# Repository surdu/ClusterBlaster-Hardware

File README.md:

# ClusterBlaster Hardware

Here you can find the schematic & PCB for the [ClusterBaster software](https://github.com/surdu/ClusterBlaster).

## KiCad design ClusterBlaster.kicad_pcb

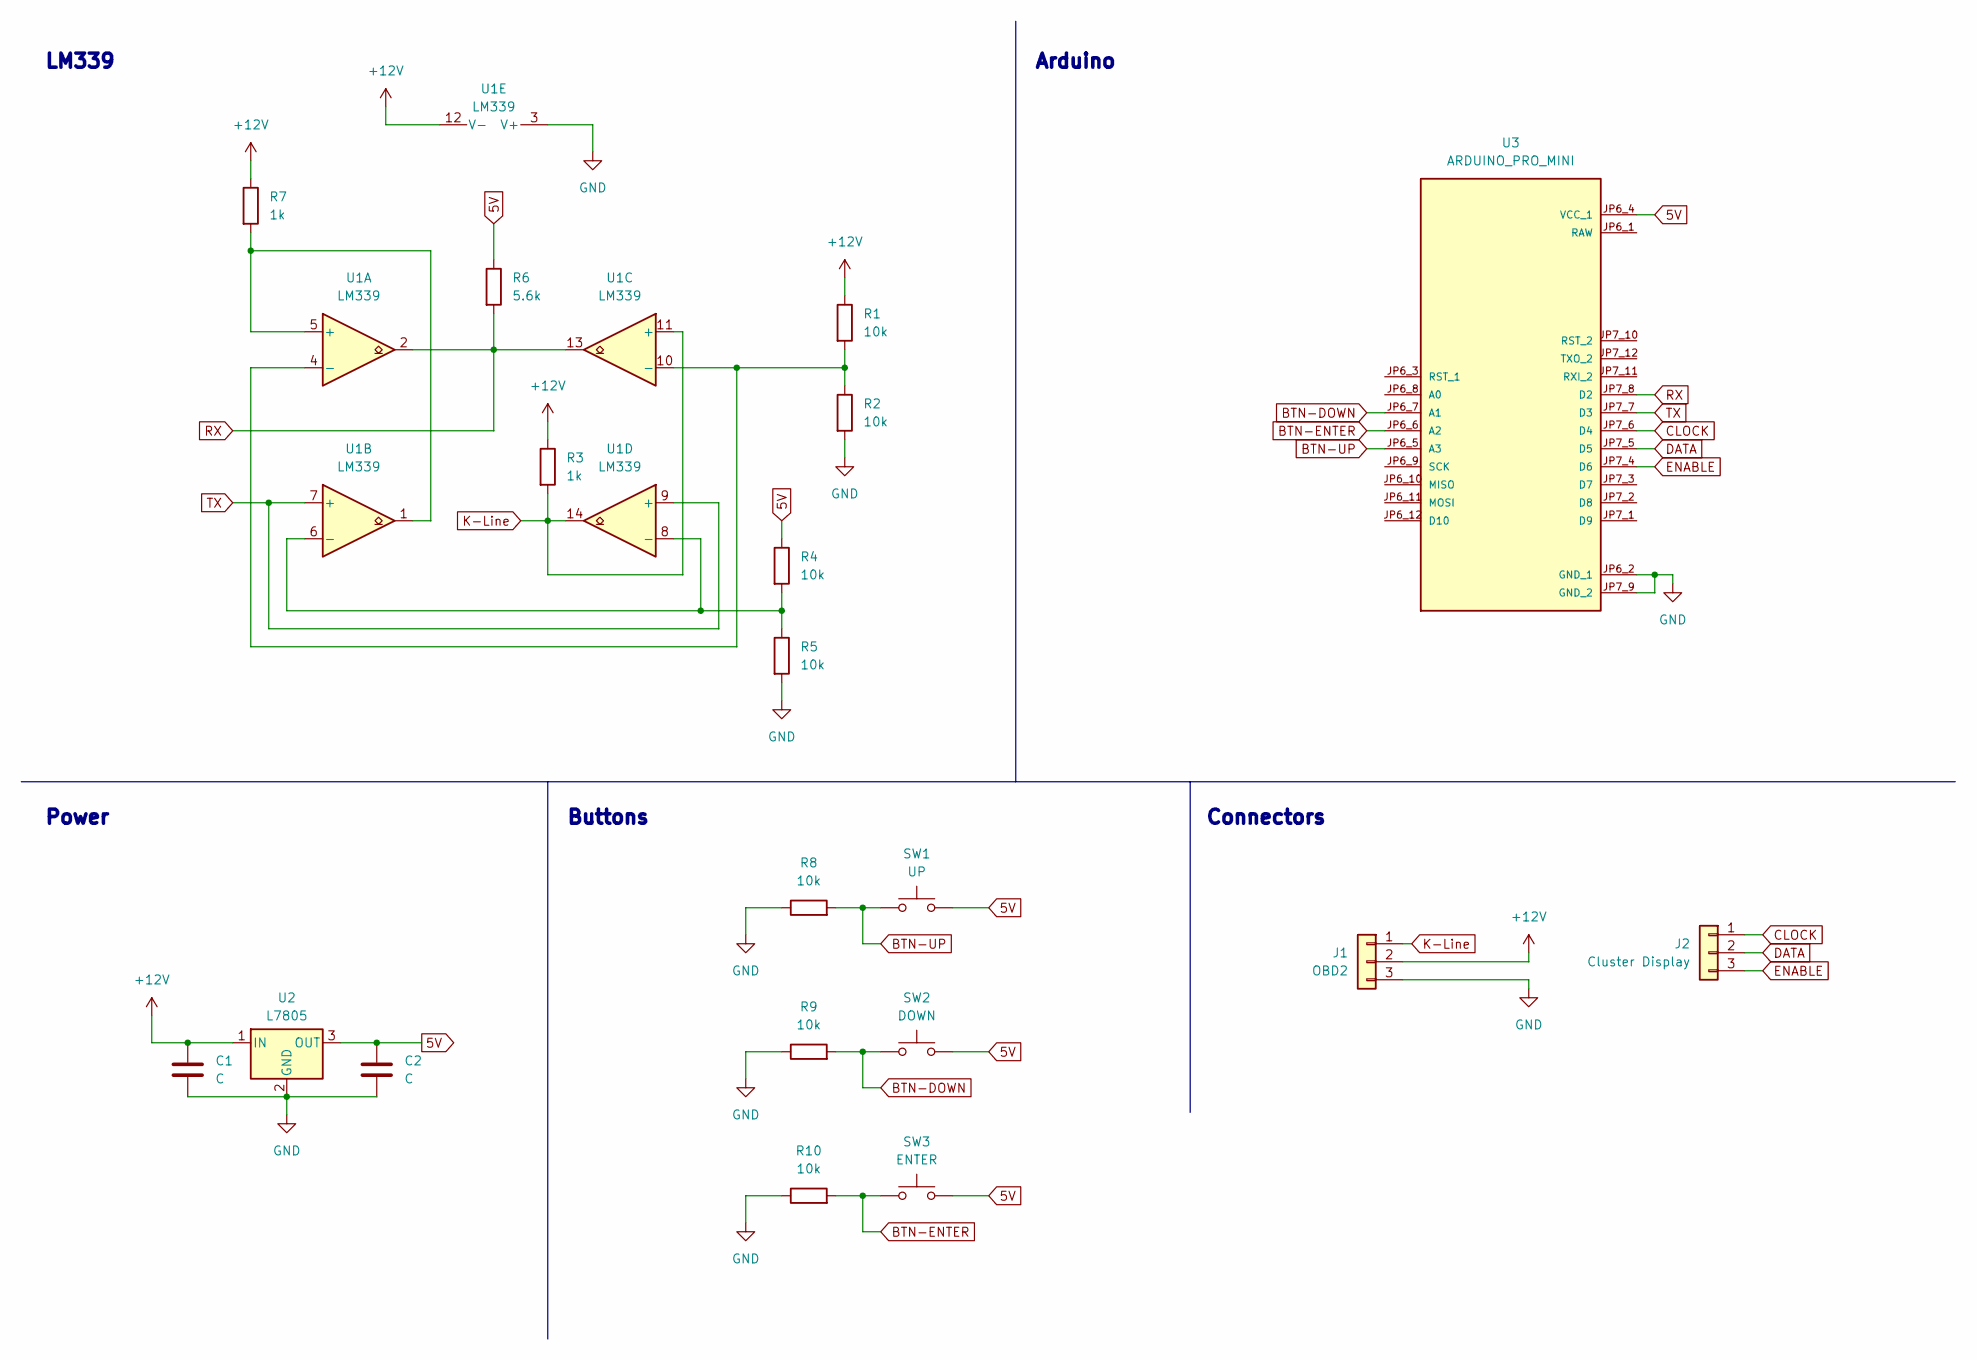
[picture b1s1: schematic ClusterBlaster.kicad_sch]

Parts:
C1, C2: C; C_0805_2012Metric
J1: OBD2; JST_XH_B3B-XH-A_1x03_P2.50mm_Vertical
J2: Cluster Display; JST_XH_B3B-XH-A_1x03_P2.50mm_Vertical
R1, R2, R4, R5, R8, R9, R10: 10k; R_0805_2012Metric
R3, R7: 1k; R_0805_2012Metric
R6: 5.6k; R_0805_2012Metric
SW1: UP; SW_PUSH_6mm
SW2: DOWN; SW_PUSH_6mm
SW3: ENTER; SW_PUSH_6mm
U1: LM339; SO-14_3.9x8.65mm_P1.27mm
U2: L7805; TO-252-3_TabPin2
U3: ARDUINO_PRO_MINI; SMD; PARTREV N/A

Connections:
5V: C2.1, R4.1, R6.1, SW1.2, SW2.2, SW3.2, U2.3 (OUT), U3.JP6_4 (VCC_1)
+12V: C1.1, J1.2, R1.1, R3.1, R7.1, U1.12 (V-), U2.1 (IN)
BTN-DOWN: R9.2, SW2.1, U3.JP6_7 (A1)
BTN-ENTER: R10.2, SW3.1, U3.JP6_6 (A2)
BTN-UP: R8.2, SW1.1, U3.JP6_5 (A3)
CLOCK: J2.1, U3.JP7_6 (D4)
DATA: J2.2, U3.JP7_5 (D5)
ENABLE: J2.3, U3.JP7_4 (D6)
GND: C1.2, C2.2, J1.3, R2.2, R5.2, R8.1, R9.1, R10.1, U1.3 (V+), U2.2 (GND), U3.JP6_2 (GND_1), U3.JP7_9 (GND_2)
K-Line: J1.1, R3.2, U1.11 (+), U1.14
unnamed: R7.2, U1.1, U1.5 (+)
unnamed: R1.2, R2.1, U1.4 (-), U1.10 (-)
unnamed: R4.2, R5.1, U1.6 (-), U1.8 (-)
RX: R6.2, U1.2, U1.13, U3.JP7_8 (D2)
TX: U1.7 (+), U1.9 (+), U3.JP7_7 (D3)

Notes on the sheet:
Arduino
LM339
Buttons
Power
Connectors

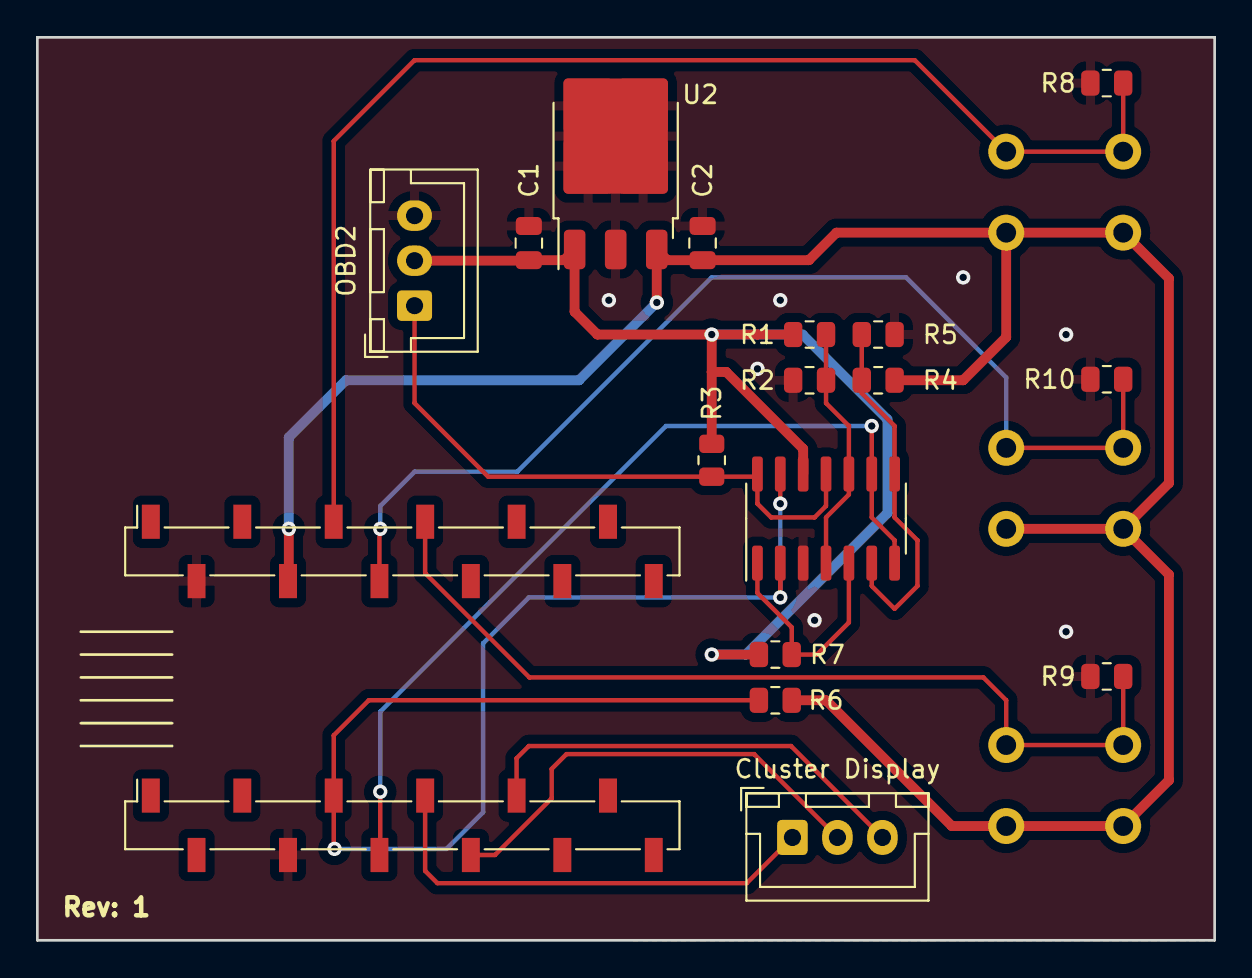
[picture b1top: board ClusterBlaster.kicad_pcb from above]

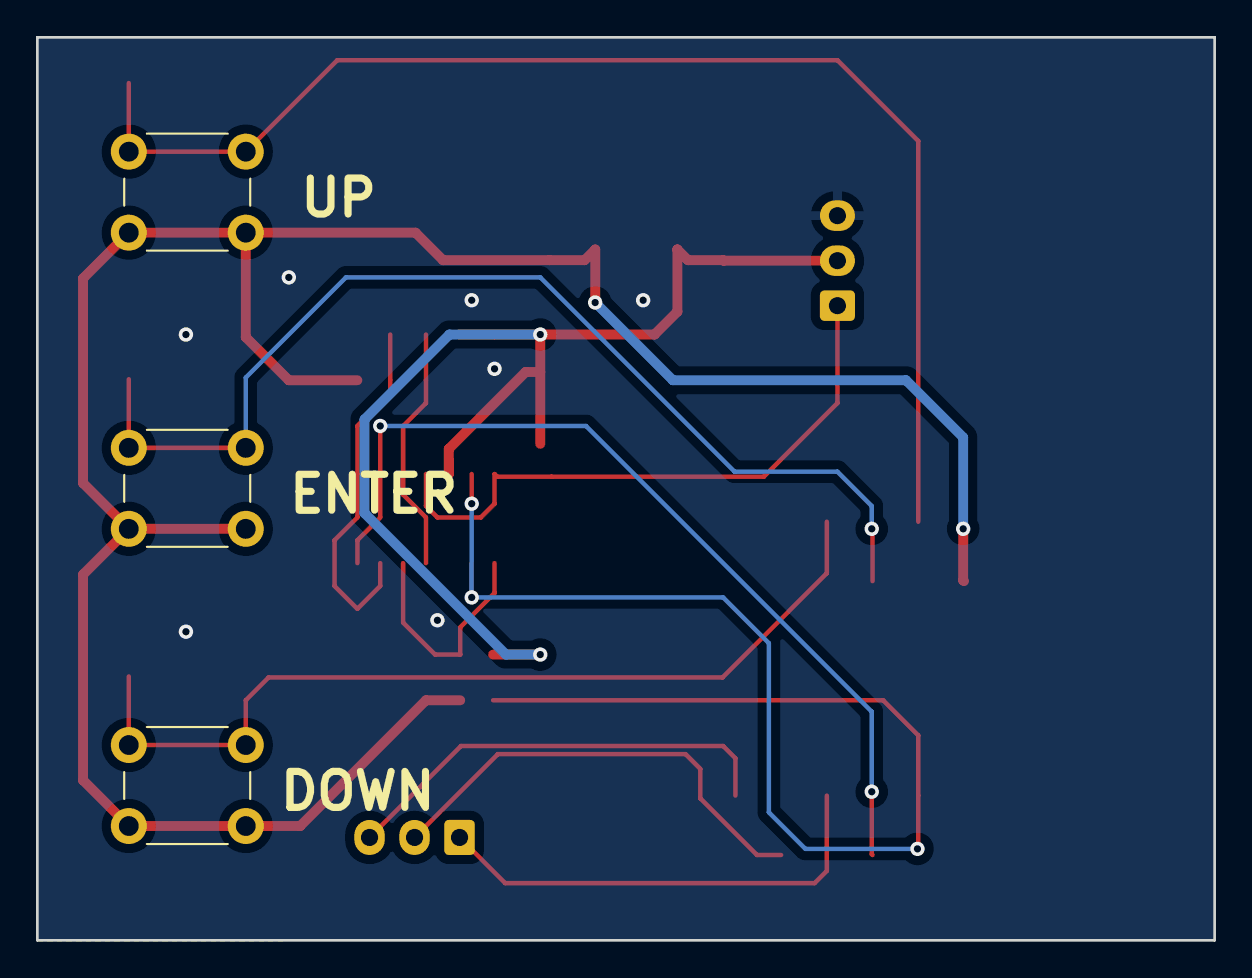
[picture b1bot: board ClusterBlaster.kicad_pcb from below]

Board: 2 copper layers, 65.4 x 50.2 mm, 20 parts (3 on the bottom side), 15 nets.

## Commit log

2023-09-24 Completed first draft of the schematic
2023-09-25 Added Arduino symbol and footprint
2023-09-26 Added all the components
2023-09-28 Started work on PCB layout
2023-09-30 Switched Arduino to SMD sockets
2023-10-01 Routed PCB
2023-10-13 Added logo and revision
2023-10-14 Made the schematic cleaner
2023-10-14 Added PCB image
2023-10-15 PCB improvements
